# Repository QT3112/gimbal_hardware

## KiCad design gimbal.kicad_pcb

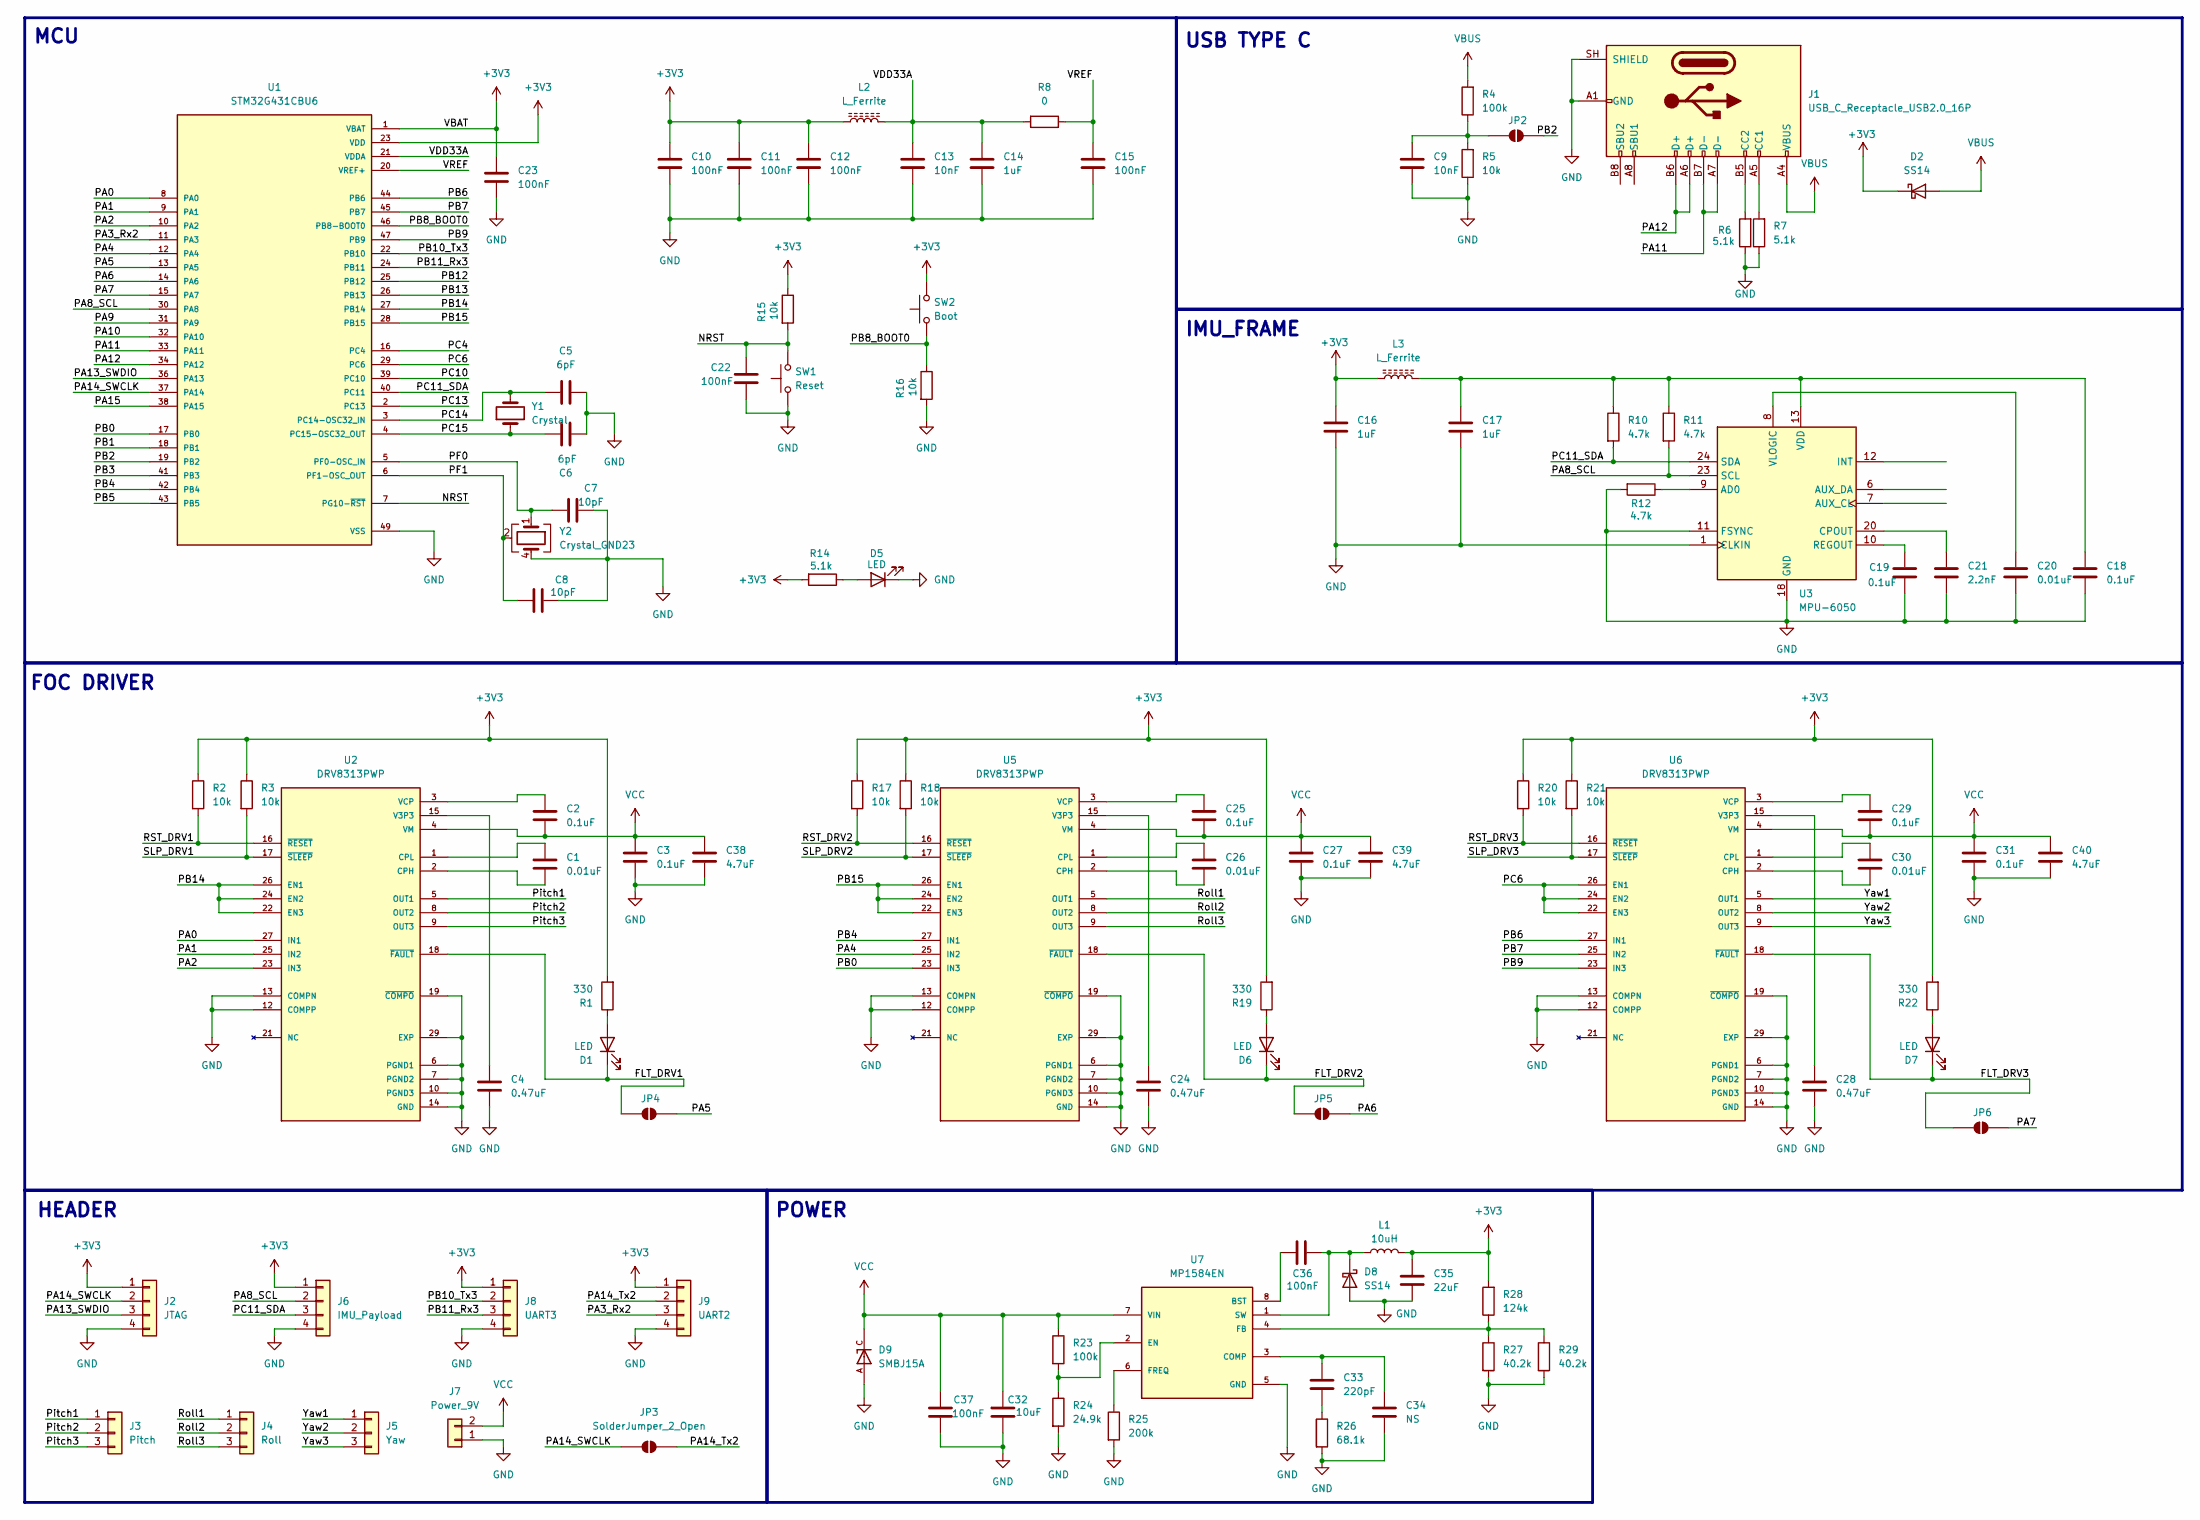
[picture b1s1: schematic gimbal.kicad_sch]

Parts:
C1, C20, C26, C30: 0.01uF; C_0201_0603Metric_Pad0.64x0.40mm_HandSolder
C2, C3, C18, C19, C25, C27, C29, C31: 0.1uF; C_0201_0603Metric_Pad0.64x0.40mm_HandSolder
C4, C24, C28: 0.47uF; C_0201_0603Metric_Pad0.64x0.40mm_HandSolder
C5, C6: 6pF; C_0201_0603Metric_Pad0.64x0.40mm_HandSolder
C7, C8: 10pF; C_0201_0603Metric_Pad0.64x0.40mm_HandSolder
C9, C13: 10nF; C_0201_0603Metric_Pad0.64x0.40mm_HandSolder
C10, C11, C12, C15, C22, C23, C36, C37: 100nF; C_0201_0603Metric_Pad0.64x0.40mm_HandSolder
C14, C16, C17: 1uF; C_0201_0603Metric_Pad0.64x0.40mm_HandSolder
C21: 2.2nF; C_0201_0603Metric_Pad0.64x0.40mm_HandSolder
C32: 10uF; C_0805_2012Metric_Pad1.18x1.45mm_HandSolder
C33: 220pF; C_0201_0603Metric_Pad0.64x0.40mm_HandSolder
C34: NS; C_0201_0603Metric_Pad0.64x0.40mm_HandSolder
C35: 22uF; C_0201_0603Metric_Pad0.64x0.40mm_HandSolder
C38, C39, C40: 4.7uF; C_0201_0603Metric_Pad0.64x0.40mm_HandSolder
D1, D5, D6, D7: LED; LED_0603_1608Metric
D2, D8: SS14; D_SMA
D9: SMBJ15A; DIOM4336X265N; PARTREV F2102
J1: USB_C_Receptacle_USB2.0_16P; USB_C_Receptacle_GCT_USB4110
J2: JTAG; PinHeader_1x04_P2.54mm_Vertical
J3: Pitch; PinHeader_1x03_P2.54mm_Vertical
J4: Roll; PinHeader_1x03_P2.54mm_Vertical
J5: Yaw; PinHeader_1x03_P2.54mm_Vertical
J6: IMU_Payload; JST_GH_SM04B-GHS-TB_1x04-1MP_P1.25mm_Horizontal
J7: Power_9V; AMASS_XT30U-F_1x02_P5.0mm_Vertical
J8: UART3; JST_GH_SM04B-GHS-TB_1x04-1MP_P1.25mm_Horizontal
J9: UART2; JST_GH_SM04B-GHS-TB_1x04-1MP_P1.25mm_Horizontal
JP2, JP4, JP5, JP6: SolderJumper-2_P1.3mm_Open_RoundedPad1.0x1.5mm
JP3: SolderJumper_2_Open; SolderJumper-2_P1.3mm_Open_RoundedPad1.0x1.5mm
L1: 10uH; L_7.3x7.3_H3.5
L2: L_Ferrite; L_0201_0603Metric_Pad0.64x0.40mm_HandSolder
L3: L_Ferrite; L_0201_0603Metric
R1, R19, R22: 330; R_0201_0603Metric_Pad0.64x0.40mm_HandSolder
R2, R3, R5, R15, R16, R17, R18, R20, R21: 10k; R_0201_0603Metric_Pad0.64x0.40mm_HandSolder
R4, R23: 100k; R_0201_0603Metric_Pad0.64x0.40mm_HandSolder
R6, R7, R14: 5.1k; R_0201_0603Metric_Pad0.64x0.40mm_HandSolder
R8: 0; R_0201_0603Metric_Pad0.64x0.40mm_HandSolder
R10, R11, R12: 4.7k; R_0201_0603Metric_Pad0.64x0.40mm_HandSolder
R24: 24.9k; R_0201_0603Metric_Pad0.64x0.40mm_HandSolder
R25: 200k; R_0201_0603Metric_Pad0.64x0.40mm_HandSolder
R26: 68.1k; R_0201_0603Metric_Pad0.64x0.40mm_HandSolder
R27, R29: 40.2k; R_0201_0603Metric_Pad0.64x0.40mm_HandSolder
R28: 124k; R_0201_0603Metric_Pad0.64x0.40mm_HandSolder
SW1: Reset; SW_SPST_B3U-1000P
SW2: Boot; SW_SPST_B3U-1000P
U1: STM32G431CBU6; QFN50P700X700X60-49N; PARTREV 6
U2, U5, U6: DRV8313PWP; SOP65P640X120-29N; PARTREV D
U3: MPU-6050; InvenSense_QFN-24_4x4mm_P0.5mm
U7: MP1584EN; SOIC127P600X170-9N
Y1: Crystal; Crystal_SMD_2012-2Pin_2.0x1.2mm_HandSoldering
Y2: Crystal_GND23; Crystal_SMD_2016-4Pin_2.0x1.6mm

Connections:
+3V3: C10.2, C11.2, C12.2, C16.1, C23.2, C35.1, D2.1 (K), J2.1, J6.1, J8.1, J9.1, L1.2, L2.1, L3.1, R1.2, R2.1, R3.1, R14.2, R15.1, R17.1, R18.1, R19.2, R20.1, R21.1, R22.2, R28.2, SW2.2, U1.1 (VBAT), U1.23 (VDD), U1.35 (VDD), U1.48 (VDD)
/FLT_DRV1: D1.1 (K), JP4.1 (A), U2.18 (~FAULT)
/FLT_DRV2: D6.1 (K), JP5.1 (A), U5.18 (~FAULT)
/FLT_DRV3: D7.1 (K), JP6.1 (A), U6.18 (~FAULT)
/NRST: C22.2, R15.2, SW1.2, U1.7 (PG10-~RST)
/PA0: U1.8 (PA0), U2.27 (IN1)
/PA1: U1.9 (PA1), U2.25 (IN2)
/PA2: U1.10 (PA2), U2.23 (IN3)
/PA3_Rx2: J9.3, U1.11 (PA3)
/PA4: U1.12 (PA4), U5.25 (IN2)
/PA5: JP4.2 (B), U1.13 (PA5)
/PA6: JP5.2 (B), U1.14 (PA6)
/PA7: JP6.2 (B), U1.15 (PA7)
/PA8_SCL: J6.2, R11.2, U1.30 (PA8), U3.23 (SCL)
/PA9: U1.31 (PA9)
/PA10: U1.32 (PA10)
/PA11: J1.A7 (D-), J1.B7 (D-), U1.33 (PA11)
/PA12: J1.A6 (D+), J1.B6 (D+), U1.34 (PA12)
/PA13_SWDIO: J2.3, U1.36 (PA13)
/PA14_SWCLK: J2.2, JP3.1 (A), U1.37 (PA14)
/PA14_Tx2: J9.2, JP3.2 (B)
/PA15: U1.38 (PA15)
/PB0: U1.17 (PB0), U5.23 (IN3)
/PB1: U1.18 (PB1)
/PB2: JP2.2 (B), U1.19 (PB2)
/PB3: U1.41 (PB3)
/PB4: U1.42 (PB4), U5.27 (IN1)
/PB5: U1.43 (PB5)
/PB6: U1.44 (PB6), U6.27 (IN1)
/PB7: U1.45 (PB7), U6.25 (IN2)
/PB8_BOOT0: R16.1, SW2.1, U1.46 (PB8-BOOT0)
/PB9: U1.47 (PB9), U6.23 (IN3)
/PB10_Tx3: J8.2, U1.22 (PB10)
/PB11_Rx3: J8.3, U1.24 (PB11)
/PB12: U1.25 (PB12)
/PB13: U1.26 (PB13)
/PB14: U1.27 (PB14), U2.22 (EN3), U2.24 (EN2), U2.26 (EN1)
/PB15: U1.28 (PB15), U5.22 (EN3), U5.24 (EN2), U5.26 (EN1)
/PC4: U1.16 (PC4)
/PC6: U1.29 (PC6), U6.22 (EN3), U6.24 (EN2), U6.26 (EN1)
/PC10: U1.39 (PC10)
/PC11_SDA: J6.3, R10.2, U1.40 (PC11), U3.24 (SDA)
/PC13: U1.2 (PC13)
/PC14: C5.1, U1.3 (PC14-OSC32_IN), Y1.2
/PC15: C6.1, U1.4 (PC15-OSC32_OUT), Y1.1
/PF0: C7.1, U1.5 (PF0-OSC_IN), Y2.1
/PF1: C8.1, U1.6 (PF1-OSC_OUT), Y2.2 (G), Y2.3 (G)
/Pitch1: J3.1, U2.5 (OUT1)
/Pitch2: J3.2, U2.8 (OUT2)
/Pitch3: J3.3, U2.9 (OUT3)
/RST_DRV1: R2.2, U2.16 (~RESET)
/RST_DRV2: R17.2, U5.16 (~RESET)
/RST_DRV3: R20.2, U6.16 (~RESET)
/Roll1: J4.1, U5.5 (OUT1)
/Roll2: J4.2, U5.8 (OUT2)
/Roll3: J4.3, U5.9 (OUT3)
/SLP_DRV1: R3.2, U2.17 (~SLEEP)
/SLP_DRV2: R18.2, U5.17 (~SLEEP)
/SLP_DRV3: R21.2, U6.17 (~SLEEP)
/VDD33A: C13.2, C14.2, L2.2, R8.2, U1.21 (VDDA)
/VREF: C15.2, R8.1, U1.20 (VREF+)
/Yaw1: J5.1, U6.5 (OUT1)
/Yaw2: J5.2, U6.8 (OUT2)
/Yaw3: J5.3, U6.9 (OUT3)
GND: C3.2, C4.2, C5.2, C6.2, C7.2, C8.2, C9.1, C10.1, C11.1, C12.1, C13.1, C14.1, C15.1, C16.2, C17.2, C18.2, C19.2, C20.2, C21.2, C22.1, C23.1, C24.2, C27.2, C28.2, C31.2, C32.2, C34.2, C35.2, C37.2, C38.2, C39.2, C40.2, D5.1 (K), D8.2 (A), D9.A, J1.A1 (GND), J1.A12 (GND), J1.B1 (GND), J1.B12 (GND), J1.SH (SHIELD), J2.4, J6.4, J7.1, J8.4, J9.4, R5.1, R6.1, R7.1, R12.2, R16.2, R24.2, R25.2, R26.2, R27.2, R29.2, SW1.1, U1.49 (VSS), U2.6 (PGND1), U2.7 (PGND2), U2.10 (PGND3), U2.12 (COMPP), U2.13 (COMPN), U2.14 (GND), U2.19 (~COMPO), U2.20 (GND), U2.28 (GND), U2.29 (EXP), U3.1 (CLKIN), U3.11 (FSYNC), U3.18 (GND), U5.6 (PGND1), U5.7 (PGND2), U5.10 (PGND3), U5.12 (COMPP), U5.13 (COMPN), U5.14 (GND), U5.19 (~COMPO), U5.20 (GND), U5.28 (GND), U5.29 (EXP), U6.6 (PGND1), U6.7 (PGND2), U6.10 (PGND3), U6.12 (COMPP), U6.13 (COMPN), U6.14 (GND), U6.19 (~COMPO), U6.20 (GND), U6.28 (GND), U6.29 (EXP), U7.5 (GND), U7.9 (GND), Y2.4
unnamed: C33.2, R26.1
unnamed: D1.2 (A), R1.1
unnamed: D5.2 (A), R14.1
unnamed: D6.2 (A), R19.1
unnamed: D7.2 (A), R22.1
unnamed: C36.1, D8.1 (K), L1.1, U7.1 (SW)
unnamed: J1.A5 (CC1), R7.2
unnamed: J1.B5 (CC2), R6.2
unnamed: C9.2, JP2.1 (A), R4.1, R5.2
unnamed: C1.2, U2.2 (CPH)
unnamed: C1.1, U2.1 (CPL)
unnamed: C4.1, U2.15 (V3P3)
unnamed: C2.1, U2.3 (VCP)
unnamed: R12.1, U3.9 (AD0)
unnamed: C21.1, U3.20 (CPOUT)
unnamed: C19.1, U3.10 (REGOUT)
unnamed: C17.1, C18.1, L3.2, R10.1, R11.1, U3.13 (VDD)
unnamed: C20.1, U3.8 (VLOGIC)
unnamed: C26.2, U5.2 (CPH)
unnamed: C26.1, U5.1 (CPL)
unnamed: C24.1, U5.15 (V3P3)
unnamed: C25.1, U5.3 (VCP)
unnamed: C30.2, U6.2 (CPH)
unnamed: C30.1, U6.1 (CPL)
unnamed: C28.1, U6.15 (V3P3)
unnamed: C29.1, U6.3 (VCP)
unnamed: C36.2, U7.8 (BST)
unnamed: C33.1, C34.1, U7.3 (COMP)
unnamed: R23.2, R24.1, U7.2 (EN)
unnamed: R27.1, R28.1, R29.1, U7.4 (FB)
unnamed: R25.1, U7.6 (FREQ)
VBUS: D2.2 (A), J1.A4 (VBUS), J1.A9 (VBUS), J1.B4 (VBUS), J1.B9 (VBUS), R4.2
VCC: C2.2, C3.1, C25.2, C27.1, C29.2, C31.1, C32.1, C37.1, C38.1, C39.1, C40.1, D9.C, J7.2, R23.1, U2.4 (VM), U2.11 (VM), U5.4 (VM), U5.11 (VM), U6.4 (VM), U6.11 (VM), U7.7 (VIN)

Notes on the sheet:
FOC DRIVER
HEADER
USB TYPE C
POWER
MCU
IMU_FRAME

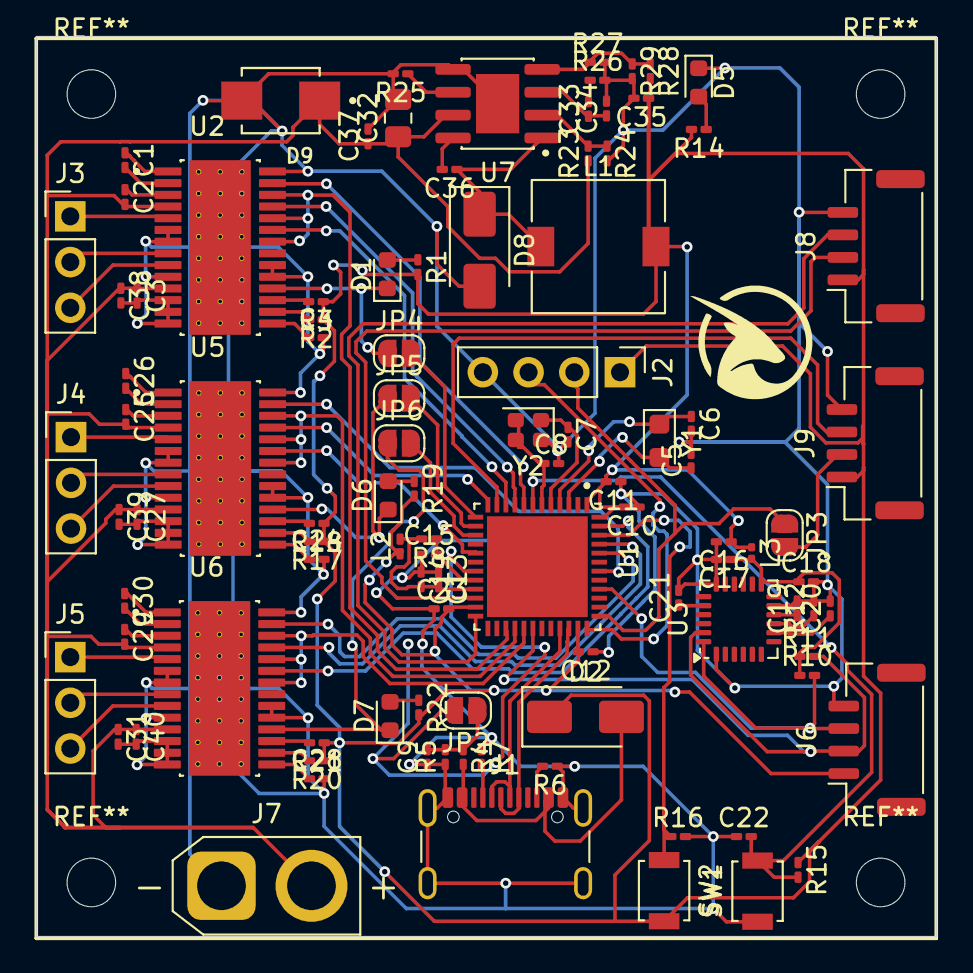
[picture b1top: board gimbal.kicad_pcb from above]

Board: 2 copper layers, 50.0 x 50.0 mm, 101 parts (0 on the bottom side), 87 nets.

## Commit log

2026-06-22 schematic
